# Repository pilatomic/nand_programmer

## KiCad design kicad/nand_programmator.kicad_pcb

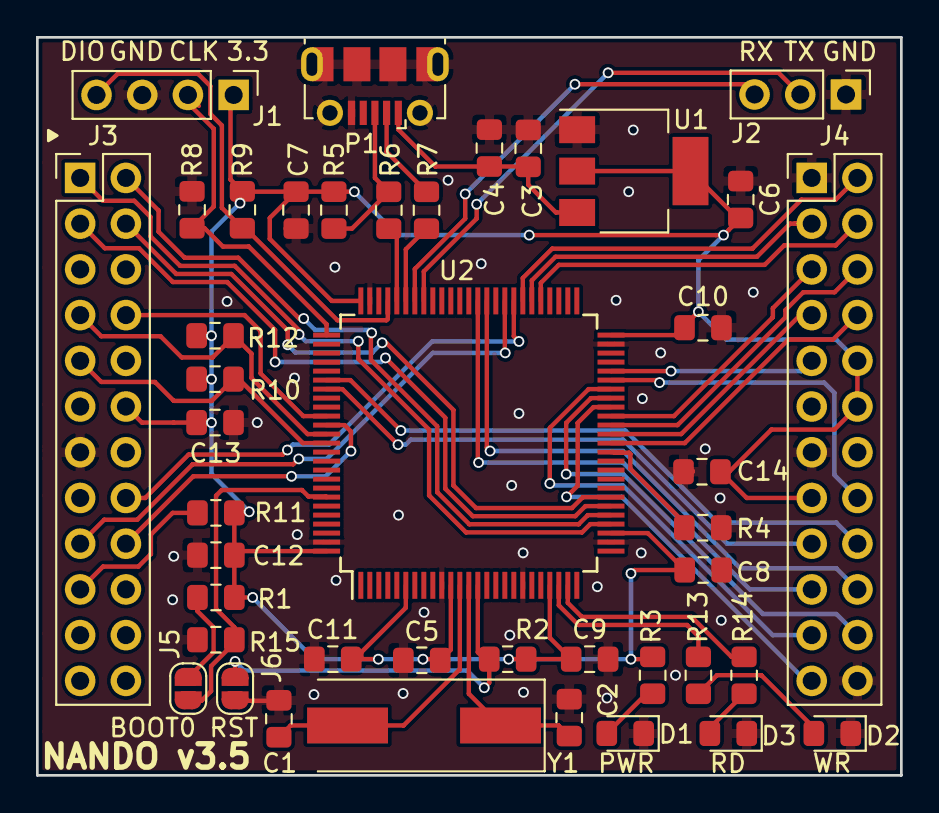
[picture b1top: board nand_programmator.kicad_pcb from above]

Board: 2 copper layers, 48.0 x 41.0 mm, 42 parts (0 on the bottom side), 49 nets.

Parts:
C1, C2: 30pF; C_0805_2012Metric_Pad1.15x1.40mm_HandSolder
C3, C6: 10uF; C_0805_2012Metric_Pad1.15x1.40mm_HandSolder
C4, C5, C7, C8, C9, C10, C11, C12, C13, C14: 0.1uF; C_0805_2012Metric_Pad1.15x1.40mm_HandSolder
D1: GREEN; LED_0805_2012Metric_Pad1.15x1.40mm_HandSolder
D2: RED; LED_0805_2012Metric_Pad1.15x1.40mm_HandSolder
D3: YELLOW; LED_0805_2012Metric_Pad1.15x1.40mm_HandSolder
J1: Conn_01x04; PinHeader_1x04_P2.54mm_Vertical
J2: Conn_01x03; PinHeader_1x03_P2.54mm_Vertical
J3: Conn_02x12_Odd_Even_Left; PinHeader_2x12_P2.54mm_Vertical
J4: Conn_02x12_Odd_Even_Right; PinHeader_2x12_P2.54mm_Vertical_2
J5: BOOT0; SolderJumper-2_P1.3mm_Open_RoundedPad1.0x1.5mm
J6: ~RST; SolderJumper-2_P1.3mm_Open_RoundedPad1.0x1.5mm
P1: USB; USB_Micro-B_Molex-105017-0001
R1: 510; R_0805_2012Metric_Pad1.15x1.40mm_HandSolder
R2, R4, R8, R9, R10, R11, R12, R15: 10k; R_0805_2012Metric_Pad1.15x1.40mm_HandSolder
R3, R13, R14: 1k; R_0805_2012Metric_Pad1.15x1.40mm_HandSolder
R5: 1.5k; R_0805_2012Metric_Pad1.15x1.40mm_HandSolder
R6, R7: 22; R_0805_2012Metric_Pad1.15x1.40mm_HandSolder
U1: LM1117-3.3; SOT-223
U2: STM32F103VCT6; LQFP-100_14x14mm_Pitch0.5mm
Y1: Crystal_SMD_8MHz_18pF; Crystal_SMD_HC49-SD

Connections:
+3V3: C5.1, C6.1, C7.1, C8.1, C9.1, C10.1, C11.1, C12.1, C13.2, C14.2, J1.1, J3.12, J4.34, J4.37, J4.39, R1.1, R2.1, R3.2, R5.2, R9.1, R10.2, R11.2, R12.1, U1.2, U1.4, U2.6, U2.11, U2.22, U2.28, U2.50, U2.75, U2.100
+5V: C3.1, C4.1, P1.1, U1.3
/BOOT0: J5.1, R15.2, U2.94
/FSMC_ALE: J3.17, U2.59
/FSMC_CLE: J3.16, U2.58
/FSMC_D0: J4.29, U2.61
/FSMC_D1: J4.30, U2.62
/FSMC_D2: J4.31, U2.81
/FSMC_D3: J4.32, U2.82
/FSMC_D4: J4.41, U2.38
/FSMC_D5: J4.42, U2.39
/FSMC_D6: J4.43, U2.40
/FSMC_D7: J4.44, U2.41
/FSMC_D8: J4.26, U2.42
/FSMC_D9: J4.27, U2.43
/FSMC_D10: J4.28, U2.44
/FSMC_D11: J4.33, U2.45
/FSMC_D12: J4.40, U2.46
/FSMC_D13: J4.45, U2.55
/FSMC_D14: J4.46, U2.56
/FSMC_D15: J4.47, U2.57
/FSMC_NCE2: J3.9, R10.1, U2.88
/FSMC_NOE: J3.8, U2.85
/FSMC_NWAIT: J3.7, R12.2, U2.87
/FSMC_NWE: J3.18, U2.86
/NRST: J6.2, R2.2, U2.14
/RED: R13.2, U2.23
/SPI1_MISO: J3.3, U2.31
/SPI1_MOSI: J3.4, U2.32
/SPI1_NSS: J3.1, U2.29
/SPI1_SCK: J3.2, U2.30
/SWCLK: J1.2, R8.2, U2.76
/SWDIO: J1.4, R9.2, U2.72
/USART1_RX: J2.3, U2.69
/USART1_TX: J2.2, U2.68
/USB_DN: R7.1, U2.70
/USB_DP: R6.1, U2.71
/USB_N: P1.2, R7.2
/USB_P: P1.3, R5.1, R6.2
/YELLOW: R14.2, U2.24
GNDD: C1.2, C2.2, C3.2, C4.2, C5.2, C6.2, C7.2, C8.2, C9.2, C10.2, C11.2, C12.2, C13.1, C14.1, D1.1, D2.1, D3.1, J1.3, J2.1, J3.13, J4.25, J4.36, J4.48, J6.1, P1.5, P1.6, R4.1, R8.1, R15.1, U1.1, U2.10, U2.19, U2.27, U2.49, U2.74, U2.99
unnamed: C1.1, U2.12, Y1.2
unnamed: C2.1, U2.13, Y1.1
unnamed: D1.2, R3.1
unnamed: D2.2, R13.1
unnamed: D3.2, R14.1
unnamed: J3.19, R11.1
unnamed: J5.2, R1.2
unnamed: R4.2, U2.37

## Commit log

2020-12-08 Routed SPi tracks, added RST jumper
